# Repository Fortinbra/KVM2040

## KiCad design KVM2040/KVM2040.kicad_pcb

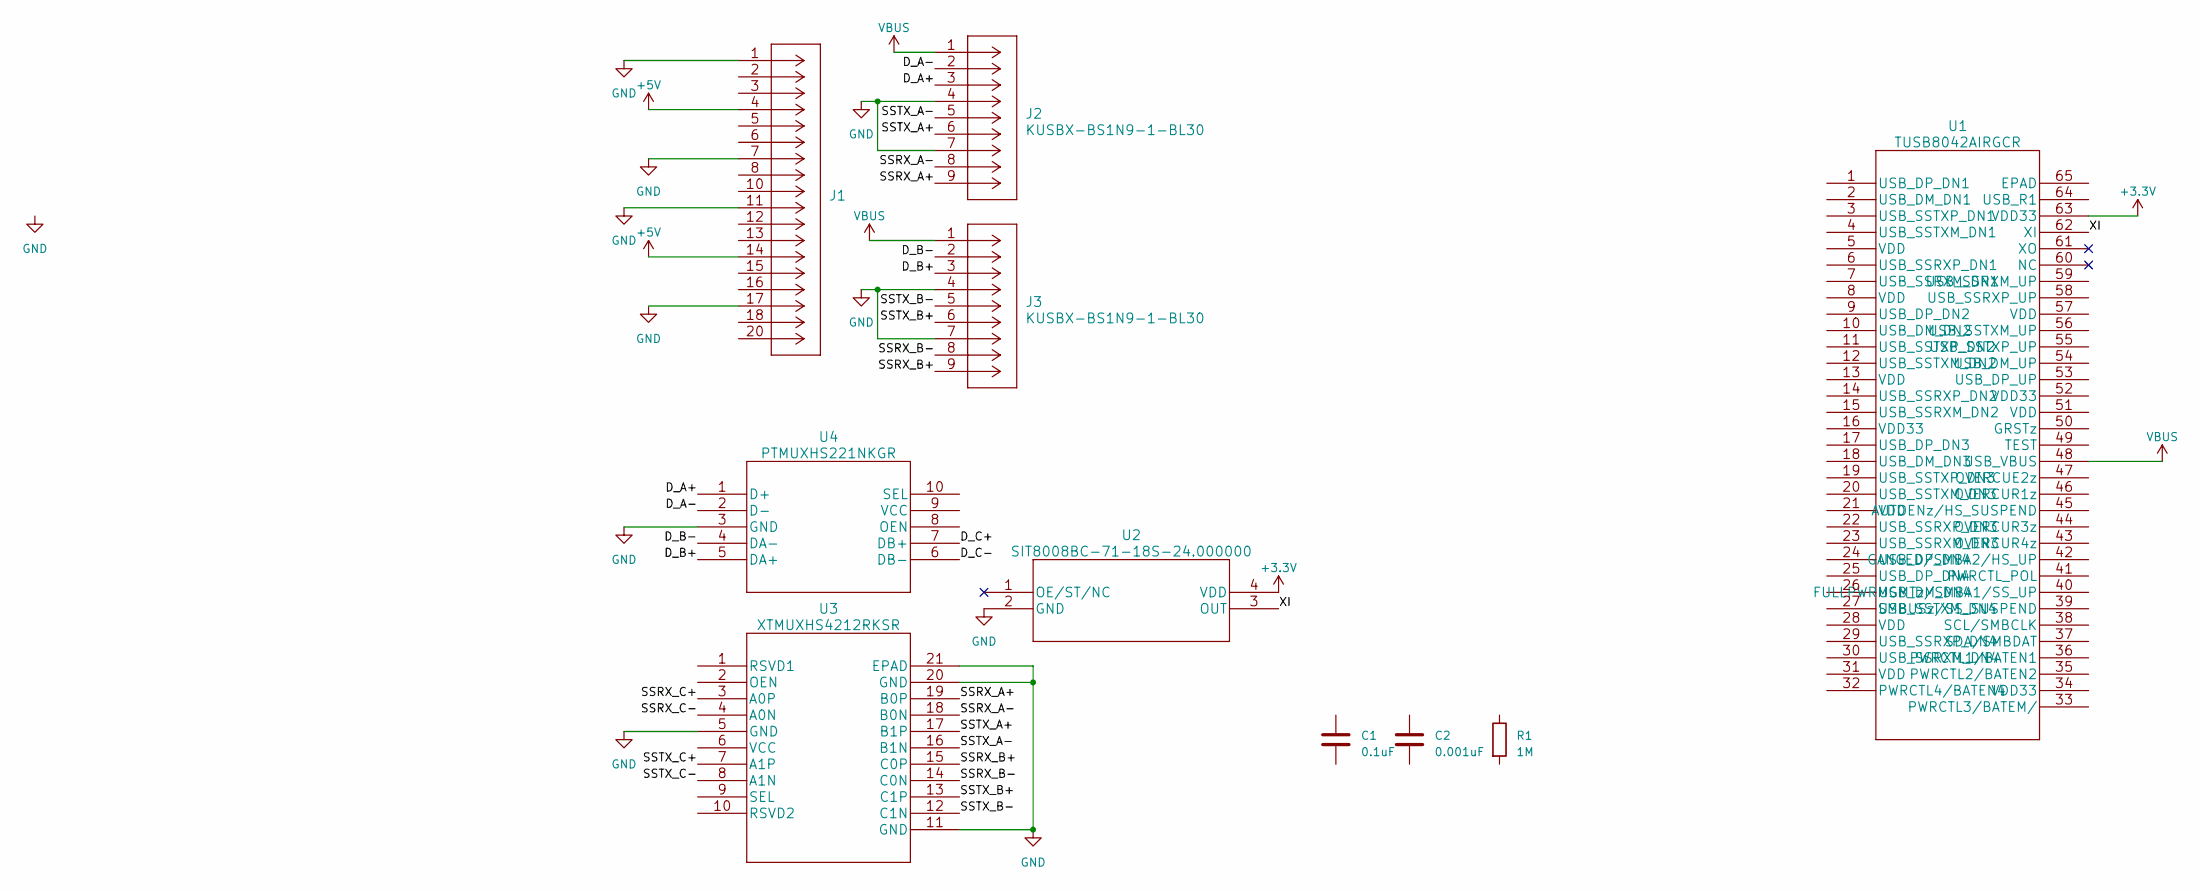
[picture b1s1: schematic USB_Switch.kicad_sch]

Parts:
C1: 0.1uF; C_0603_1608Metric
C2: 0.001uF; C_0603_1608Metric
J1: SS-52000-003
J2, J3: KUSBX-BS1N9-1-BL30
R1: 1M; R_0402_1005Metric
U1: TUSB8042AIRGCR
U2: SIT8008BC-71-18S-24.000000
U3: XTMUXHS4212RKSR
U4: PTMUXHS221NKGR

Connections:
+3.3V: U1.63 (VDD33), U2.4 (VDD)
+5V: J1.4, J1.14
/USB_Switch/D_A+: J2.3 (D+), U4.1 (D+)
/USB_Switch/D_A-: J2.2 (D-), U4.2 (D-)
/USB_Switch/D_B+: J3.3 (D+), U4.5 (DA+)
/USB_Switch/D_B-: J3.2 (D-), U4.4 (DA-)
/USB_Switch/D_C+: U4.7 (DB+)
/USB_Switch/D_C-: U4.6 (DB-)
/USB_Switch/SSRX_A+: J2.9 (STDB_SSRX+), U3.19 (B0P)
/USB_Switch/SSRX_A-: J2.8 (STDB_SSRX-), U3.18 (B0N)
/USB_Switch/SSRX_B+: J3.9 (STDB_SSRX+), U3.15 (C0P)
/USB_Switch/SSRX_B-: J3.8 (STDB_SSRX-), U3.14 (C0N)
/USB_Switch/SSRX_C+: U3.3 (A0P)
/USB_Switch/SSRX_C-: U3.4 (A0N)
/USB_Switch/SSTX_A+: J2.6 (STDB_SSTX+), U3.17 (B1P)
/USB_Switch/SSTX_A-: J2.5 (STDB_SSTX-), U3.16 (B1N)
/USB_Switch/SSTX_B+: J3.6 (STDB_SSTX+), U3.13 (C1P)
/USB_Switch/SSTX_B-: J3.5 (STDB_SSTX-), U3.12 (C1N)
/USB_Switch/SSTX_C+: U3.7 (A1P)
/USB_Switch/SSTX_C-: U3.8 (A1N)
/USB_Switch/XI: U1.62 (XI), U2.3 (OUT)
GND: J1.1, J1.7, J1.11, J1.17, J2.4 (GND), J2.7 (GND-DRAIN), J3.4 (GND), J3.7 (GND-DRAIN), U2.2 (GND), U3.5 (GND), U3.11 (GND), U3.20 (GND), U3.21 (EPAD), U4.3 (GND)
VBUS: J2.1 (VBUS), J3.1 (VBUS), U1.48 (USB_VBUS)

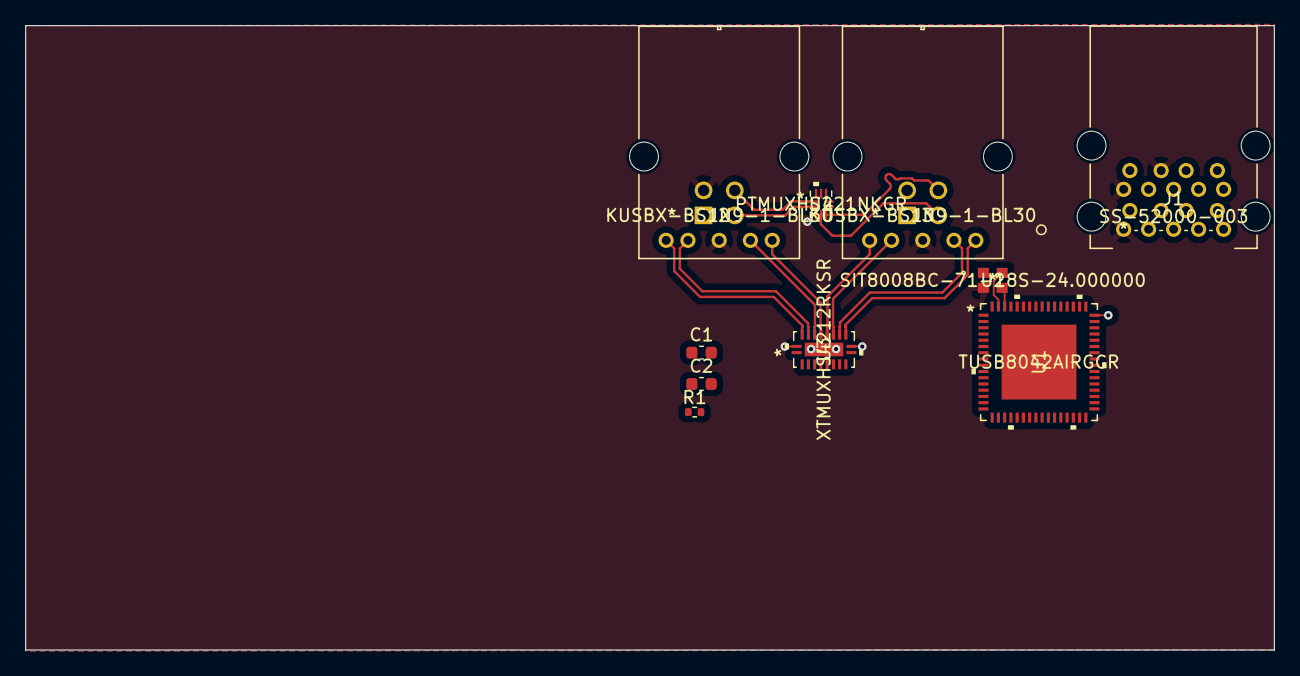
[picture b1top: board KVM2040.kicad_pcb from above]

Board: 4 copper layers, 100.0 x 50.0 mm, 10 parts (0 on the bottom side), 17 nets.

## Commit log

2023-03-15 First few parts
2023-03-15 Adding some nets
2023-03-16 Figuring out Dif pairs
2023-04-03 USB progress
2023-04-03 USB-B replacement
2023-04-05 adding upstream port

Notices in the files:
parts and their libraries:
Copyright 2021 Accelerated Designs. All rights reserved.
